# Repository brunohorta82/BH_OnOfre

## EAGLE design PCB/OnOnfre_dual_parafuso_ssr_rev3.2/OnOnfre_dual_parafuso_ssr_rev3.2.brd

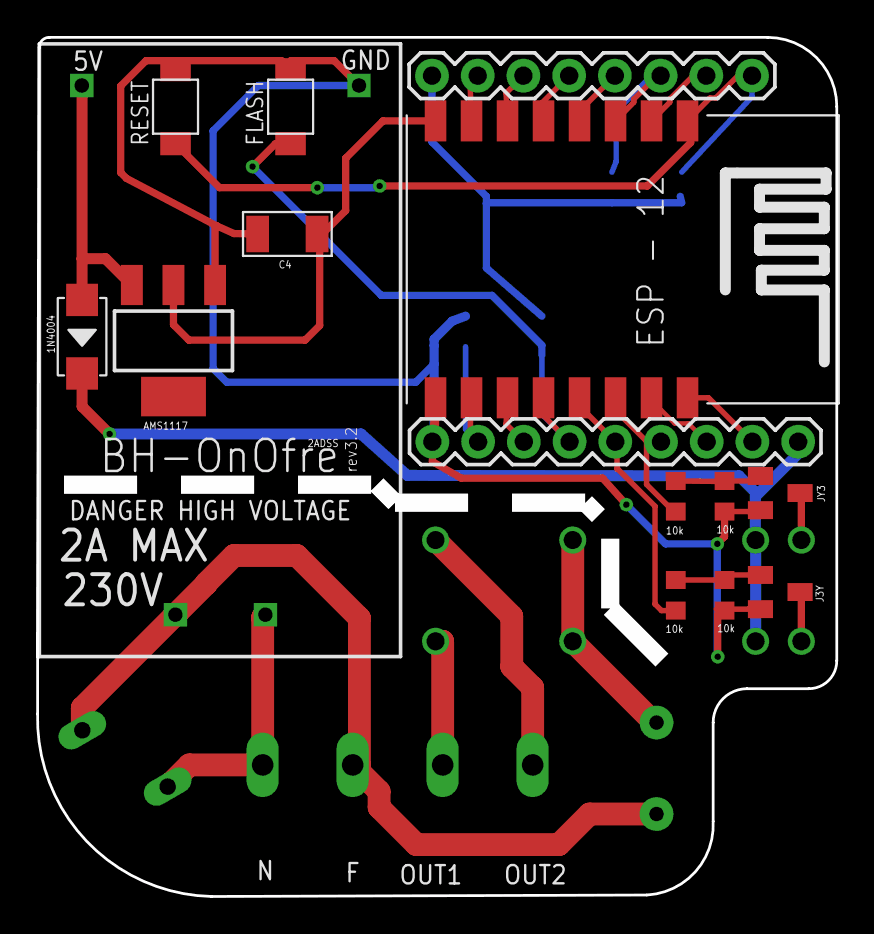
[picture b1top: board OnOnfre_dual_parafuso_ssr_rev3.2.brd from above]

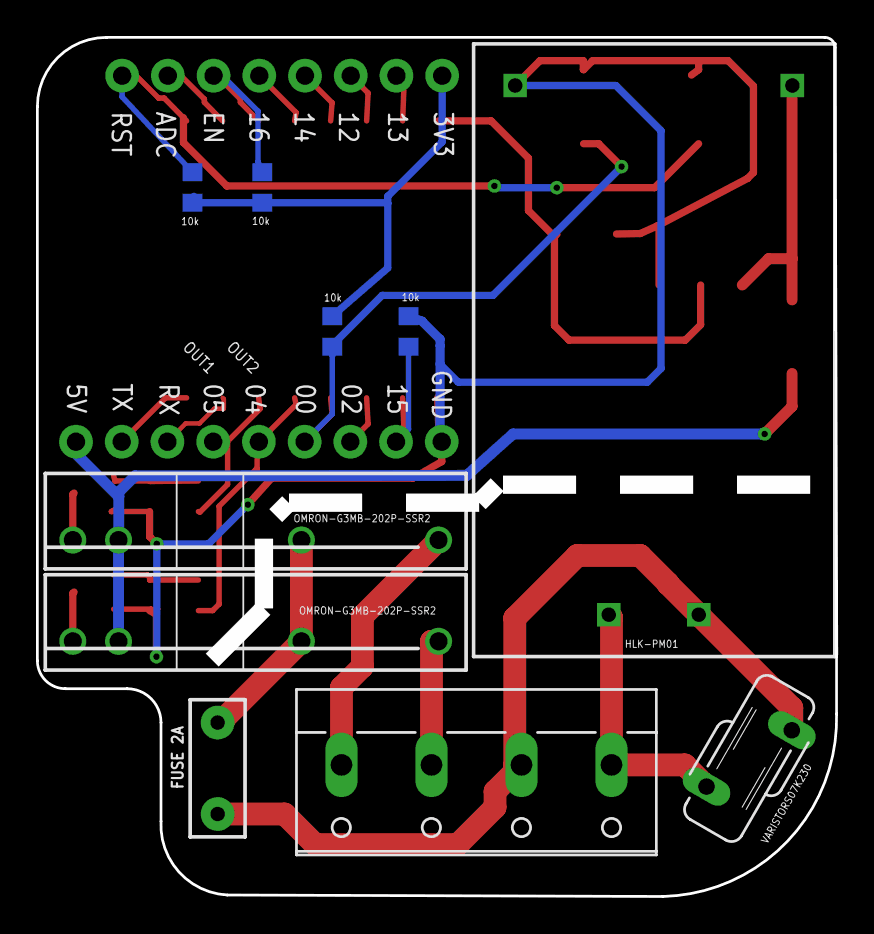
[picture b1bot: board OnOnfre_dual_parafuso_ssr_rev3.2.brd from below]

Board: 2 copper layers, 44.4 x 47.7 mm, 24 parts (10 on the bottom side), 27 nets.

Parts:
AMS1117: LM1117; SOT223
C4: 100NF; C1206
D3: 1N4004; DO-214AC
F1: FUSE 2A; PTH
FLASH: B3U-1000P-2P-SMD; B3U-1000P
J3Y: S8050; SOT23
J6: 8p; 1X09
J7: 8p; 1X08
JY3: S8050; SOT23
K1, K2: OMRON-G3MB-202P-SSR2; OMRON-G3MB-202P-SSR
R1, R2, R3, R4, R8, R9, R10, R11: 10k; R0603
R5: VARISTORS07K230; S07K230
RESET: B3U-1000P-2P-SMD; B3U-1000P
U2: esp12; ESP12-SMD
U$2: HKLPM01
X1: W237-4

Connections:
3V3: AMS1117.2, C4.1, J7.1, R8.2, R9.2, R10.2, U2.VCC
ADC: J7.7, U2.ADC
CH_PD: J7.6, R9.1, U2.CH_PD
FASE_IN: R5.1, U$2.P$1, X1.1
GND: AMS1117.1, C4.2, FLASH.2, J3Y.2, J6.1, JY3.2, R2.1, R3.1, R11.2, RESET.2, U2.GND, U$2.P$3
GPIO0: FLASH.1, J6.4, R8.1, U2.GPIO0
GPIO02: J6.3, U2.GPIO2
GPIO04: J6.6, R1.1, U2.GPIO4
GPIO05: J6.5, R4.1, U2.GPIO5
GPIO12: J7.3, U2.GPIO12
GPIO13: J7.2, U2.GPIO13
GPIO14: J7.4, U2.GPIO14
GPIO15: J6.2, R11.1, U2.GPIO15
GPIO16: J7.5, U2.GPIO16
unnamed: J3Y.3, K1.4
unnamed: J3Y.1, R3.2, R4.2
unnamed: JY3.3, K2.4
unnamed: JY3.1, R1.2, R2.2
NEUTRAL_IN: F1.P$1, R5.2, U$2.P$2, X1.2
NEUTRAL_IN_FUSED: F1.P$2, K1.2, K2.2
NEUTRAL_ONE_OUT: K1.1, X1.3
NEUTRAL_TWO_OUT: K2.1, X1.4
RESET: J7.8, R10.1, RESET.1, U2.RESET
RX: J6.7, U2.RXD0
TX: J6.8, U2.TXD0
VCC: AMS1117.3, D3.1, U$2.P$4
VCC_D: D3.2, J6.9, K1.3, K2.3

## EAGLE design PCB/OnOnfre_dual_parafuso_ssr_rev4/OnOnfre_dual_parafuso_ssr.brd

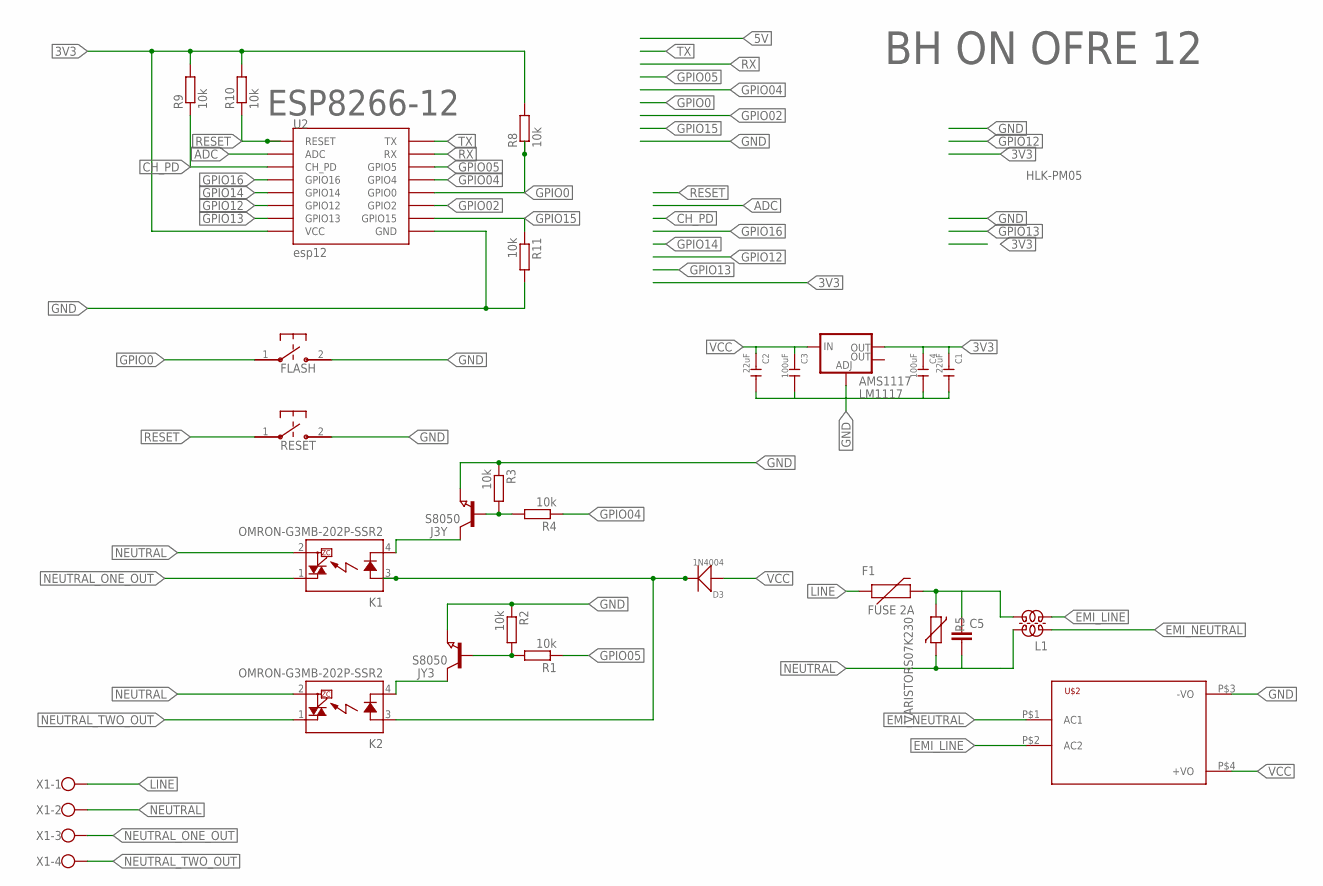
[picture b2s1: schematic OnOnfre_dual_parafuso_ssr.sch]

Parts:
AMS1117: LM1117; SOT223
C1, C2: 22uF; C1206
C3, C4: 100uF; C1206
C5: C-EU102-054X133; C102-054X133
D3: 1N4004; DO-214AC
F1: FUSE 2A; PTH
FLASH: B3U-1000P-2P-SMD; B3U-1000P
J3Y: S8050; SOT23
JY3: S8050; SOT23
K1, K2: OMRON-G3MB-202P-SSR2; OMRON-G3MB-202P-SSR
L1: ZD60820510; ZD6-2X15
R1, R2, R3, R4, R8, R9, R10, R11: 10k; R0603
R5: VARISTORS07K230; S07K230
RESET: B3U-1000P-2P-SMD; B3U-1000P
U2: esp12; ESP12-SMD
U$2: HKLPM01
X1: W237-4

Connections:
3V3: AMS1117.2 (OUT), C1.1, C4.1, R8.2, R9.2, R10.2, U2.VCC
5V: D3.2 (-), K1.3 (A), K2.3 (A)
ADC: U2.ADC
CH_PD: R9.1, U2.CH_PD
EMI_LINE: L1.2, U$2.P$2 (AC2)
EMI_NEUTRAL: L1.1, U$2.P$1 (AC1)
GND: AMS1117.1 (ADJ), C1.2, C2.2, C3.2, C4.2, FLASH.2, J3Y.2 (E), JY3.2 (E), R2.1, R3.1, R11.2, RESET.2, U2.GND, U$2.P$3 (-VO)
GPIO0: FLASH.1, R8.1, U2.GPIO0
GPIO02: U2.GPIO2
GPIO04: R4.1, U2.GPIO4
GPIO05: R1.1, U2.GPIO5
GPIO12: U2.GPIO12
GPIO13: U2.GPIO13
GPIO14: U2.GPIO14
GPIO15: R11.1, U2.GPIO15
GPIO16: U2.GPIO16
LINE: F1.P$1 (1), X1.1
unnamed: J3Y.3 (C), K1.4 (K)
unnamed: C5.1, F1.P$2 (2), L1.3, R5.2
unnamed: J3Y.1 (B), R3.2, R4.2
unnamed: JY3.3 (C), K2.4 (K)
unnamed: JY3.1 (B), R1.2, R2.2
NEUTRAL: C5.2, K1.2 (DS2), K2.2 (DS2), L1.4, R5.1, X1.2
NEUTRAL_ONE_OUT: K1.1 (DS1), X1.3
NEUTRAL_TWO_OUT: K2.1 (DS1), X1.4
RESET: R10.1, RESET.1, U2.RESET
RX: U2.RXD0 (RX)
TX: U2.TXD0 (TX)
VCC: AMS1117.3 (IN), C2.1, C3.1, D3.1 (+), U$2.P$4 (+VO)

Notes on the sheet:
HLK-PM05
BH ON OFRE 12
ESP8266-12

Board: 2 copper layers, 27 parts (8 on the bottom side), 21 nets, no tracks yet.

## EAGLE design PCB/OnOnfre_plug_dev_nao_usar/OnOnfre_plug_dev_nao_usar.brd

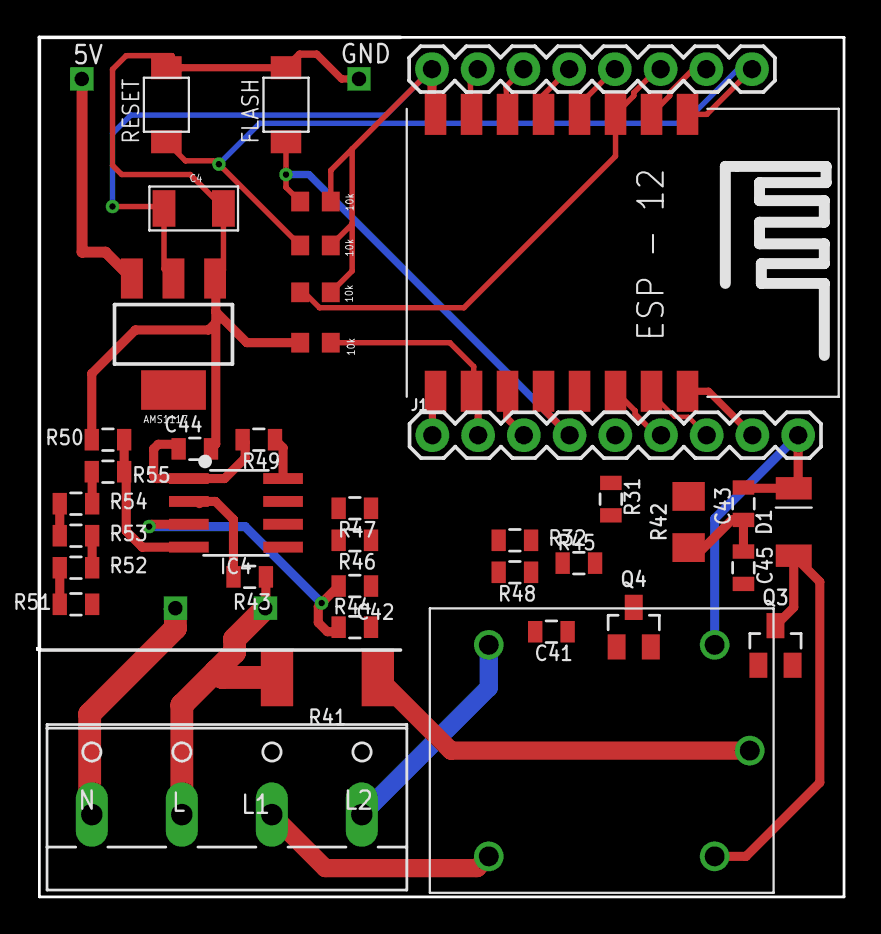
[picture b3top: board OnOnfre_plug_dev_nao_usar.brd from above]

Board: 2 copper layers, 44.7 x 47.8 mm, 40 parts (1 on the bottom side), 35 nets.

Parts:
AMS1117: LM1117; SOT223
C4: 100NF; C1206
C41, C42: 33nF; 0805
C43, C45: 100nF; 0805
C44: 1uF; 0805
D1: 1N4148; SOD80
FLASH: B3U-1000P-2P-SMD; B3U-1000P
IC4: HLW8012; SOP8
J1: 1X09
J7: 8p; 1X08
Q3, Q4: 2N7002; SOT23
R8, R9, R10, R11: 10k; R0603
R31, R43, R44, R50: 1K; 0805
R32, R45, R47, R49: 10K; 0805
R41: 0.001R; 2512
R42: 0R; 1206
R46, R48: 15K; 0805
R51, R52, R53, R54, R55: 470K; 0805
RESET: B3U-1000P-2P-SMD; B3U-1000P
RLY1: SRD-05VDC-SL-C; SRD-5VDC-SL-C
U2: esp12; ESP12-SMD
U$2: HKLPM01
X1: W237-4

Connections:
3V3: AMS1117.2, C4.1, J7.1, R8.2, R9.2, R10.2, U2.VCC
5V: C43.2, C44.2, D1.2, IC4.1, J1.9, R49.2, RLY1.COIL1
ADC: J7.7, U2.ADC
CH_PD: J7.6, R9.1, U2.CH_PD
GND: AMS1117.1, C4.2, C41.1, C42.1, C43.1, C44.1, C45.1, FLASH.2, IC4.5, J1.1, Q3.2, Q4.2, R11.2, R32.1, R42.1, R46.1, R48.1, R50.1, RESET.2, U2.GND, U$2.P$3
GPIO0: FLASH.1, J1.4, R8.1, U2.GPIO0
GPIO02: J1.3, U2.GPIO2
GPIO04: J1.5, U2.GPIO4
GPIO05: J1.6, U2.GPIO5
GPIO12: J7.3, R31.1, U2.GPIO12
GPIO13: J7.2, R45.1, R46.2, U2.GPIO13
GPIO14: J7.4, R47.1, R48.2, U2.GPIO14
GPIO15: J1.2, R11.1, U2.GPIO15
GPIO16: J7.5, U2.GPIO16
LINE_IN: R41.2, R43.2, U$2.P$1, X1.2
LINE_R: R41.1, R42.2, R44.2, RLY1.COMMON
unnamed: IC4.6, R47.2
unnamed: D1.1, Q3.3, RLY1.COIL2
unnamed: Q3.1, R31.2, R32.2
unnamed: R51.1, R52.1
unnamed: R52.2, R53.2
unnamed: IC4.8, Q4.3, R49.1
unnamed: IC4.7, R45.2
unnamed: C41.2, IC4.2, R43.1
unnamed: C42.2, IC4.3, R44.1
unnamed: R53.1, R54.1
unnamed: R54.2, R55.2
NC: RLY1.CLOSED, X1.3
NEUTRAL_IN: R51.2, U$2.P$2, X1.1
NO: RLY1.OPEN, X1.4
RESET: J7.8, R10.1, RESET.1, U2.RESET
RX: J1.7, U2.RXD0
TX: J1.8, U2.TXD0
V2P: C45.2, IC4.4, R50.2, R55.1
VCC: AMS1117.3, U$2.P$4

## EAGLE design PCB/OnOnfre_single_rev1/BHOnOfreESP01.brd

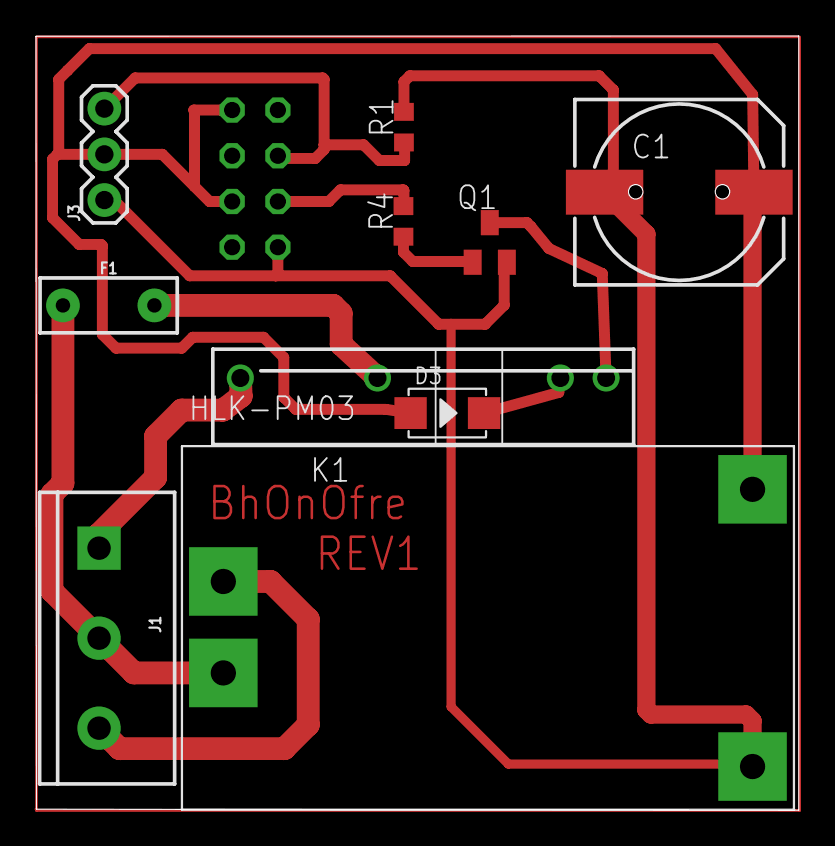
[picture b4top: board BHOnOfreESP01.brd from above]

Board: 2 copper layers, 42.4 x 43.0 mm, 11 parts (1 on the bottom side), 11 nets.

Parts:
C1: 1000uf; 140CLH-1010
D3: 1N4004; DO-214AC
F1: FUSE 2A; PTH
J1: SCREWTERMINAL-5MM-3
J3: 1X03
K1: OMRON-G3MB-202P-SSR2; OMRON-G3MB-202P-SSR
Q1: S8050; SOT23
R1, R4: 47k; R0603
U$2: HLK-PM03
U$3: ESP8266-01

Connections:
CH1: R4.2, U$3.GPIO2
GND: C1.-, J3.1, Q1.2, R1.2, U$2.-VO, U$3.GND
unnamed: K1.4, Q1.3
unnamed: J1.1, K1.1
unnamed: F1.P$1, J1.2, U$2.AC2
unnamed: J1.3, U$2.AC1
unnamed: F1.P$2, K1.2
unnamed: D3.2, K1.3
unnamed: Q1.1, R4.1
TOUCH: J3.3, R1.1, U$3.GPIO0
VCC: C1.+, D3.1, J3.2, U$2.+VO, U$3.3V3, U$3.CH_PD

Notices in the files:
parts and their libraries:
SparkFun-Connectors: Licensing: Creative Commons ShareAlike 4.0 International - https://creativecommons.org/licenses/by-sa/4.0
